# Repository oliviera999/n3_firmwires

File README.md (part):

# Firmwires – Projets ESP32 et Arduino (PlatformIO)

*Contexte : [salle aérée n³](https://n3.olution.info) · Données : [iot.olution.info](https://iot.olution.info). Voir [README racine](../README.md), [RECOMMANDATIONS_IOT](../RECOMMANDATIONS_IOT.md), [inventaire des appareils](../docs/inventaire_appareils.md).*

Dépôt regroupant **plusieurs firmwares** : deux projets principaux ESP32 (serre/aquaponie, station météo), trois projets ESP32-CAM d’envoi de photos vers un serveur web, et le kit **ratata** (ZYC0108-EN) avec exemples Arduino UNO et ESP32-CAM. Chaque projet (ou environnement) est compilable avec **PlatformIO**.

## Projets

| Projet | Dossier | Carte | Description |
|--------|---------|-------|-------------|
| **N3PhasmesProto (n3pp)** | `n3pp/` | ESP32 dev | Contrôle serre / aquaponie : température/humidité air, 4 capteurs humidité sol, pompe, luminosité, mails d’alerte, serveur web, NTP, OLED, deep sleep. |
| **MeteoStationPrototype (msp)** | `msp/` | ESP32 dev | Station météo + tracker solaire : 2× DHT, humidité sol, pluie, DS18B20, 4 LDR, 2 servos, relais, mail, serveur web, NTP, OLED. |
| **Upload Photos (unifié)** | `uploadphotosserver/` | ESP32-CAM | Un seul code, trois envs : **msp1** (msp1gallery, OTA distant HTTP, deep sleep 600 s, version courante `2.39`), **n3pp** (n3ppgallery, deep sleep 600 s, SD), **ffp3** (ffp3gallery, deep sleep 600 s). Upload et contrôle distant au réveil avec `X-Api-Key` (GET état outputs + POST version firmware, aligné serveur ≥ 5.0.306), retries de connexion, vérification du code HTTP retour. Tables `UploadPhoto*Outputs` (boards 5/6/7). Notifications mail SMTP (credentials partagés) : **une fois** au premier démarrage réel (hors réveil deep sleep, flag NVS `upcam/fb_mail`), démarrage/fin OTA, transitions matin/soir du créneau photo. `pio run -e msp1` / `-e n3pp` / `-e ffp3`. |
| **Upload Photos legacy** | `archive/uploadphotosserver_legacy/` | ESP32-CAM | Historique (`uploadphotosserver_*`) conservé en archive ; utiliser uniquement `uploadphotosserver/`. |
| **FFP5CS (aquaponie)** | `ffp5cs/` | ESP32 / ESP32-S3 | Contrôleur aquaponie (WROOM/S3), modulaire, API FFP3, réseau offline-first. Depuis v14.24, la sync distante WROOM utilise un document JSON dédié 2048 o pour absorber le payload `outputs/state` étendu (GPIO 118-123). Build WROOM plus complexe que n3pp/msp (pioarduino 2 passes) — voir [ffp5cs/docs/technical/COMPILATION_WROOM_PIOARDUINO_ET_ENVS.md](ffp5cs/docs/technical/COMPILATION_WROOM_PIOARDUINO_ET_ENVS.md). |
| **Poissonglouton (recyclage)** | `poissonglouton/` | ESP32-S3 | Compteur de bouteilles pour poubelle ludique : détection IR + ultrason (simple ou tandem), feedback audio I2S JC4827W543 (sortie speak), mode écran tactile ou headless, upload batch vers `/pgl/post-data`, heartbeat `/pgl/heartbeat` (flag `PGL_ENABLE_SERVER_HEARTBEAT`), deep sleep solaire. |
| **Banc énergie (INA226)** | `energie/` | ESP32-S3 | Banc d'essai des moniteurs de puissance INA226 du futur module d'aquaponie autonome (carte n3-universal) : panneau solaire / batterie plomb-AGM 12 V / consommation, mesure 1 Hz, POST 10 s vers `/energie-test/post-data` (famille serveur `energie`), SoC + alerte mail batterie basse, console série de calibration. Brique partagée `shared/n3_power`. Voir [energie/README.md](energie/README.md). |
| **LVGL_Widgets** | `à voir/LVGL_Widgets/` | ESP32-S3 | Interface écran tactile ; pas de serveur dédié. Dossier `à voir/` (prototype non maintenu en production). |
| **Ratata (ZYC0108-EN)** | `à voir/ratata/` | 7× UNO, 1× ESP32-CAM | Huit exemples : déplacement, servo, ultrason, évitement, suivi de ligne, voiture caméra WiFi. Dossier `à voir/`. |

## Prérequis

- [PlatformIO](https://platformio.org/) (CLI ou extension VSCode/Cursor) — **Core 6.1.19** (version épinglée en CI) :
  `pip install "platformio==6.1.19"`. PlatformIO **6.2.0** casse les builds ffp5cs WROOM pioarduino
  (`ModuleNotFoundError: SCons.Tool.FortranCommon` : tool-scons 4.8.1 remplacé par 4.11.1 en plein build).
- Selon le projet : carte **ESP32** (esp32dev), **ESP32-CAM** (esp32cam), ou **Arduino UNO** (uno)

## Compilation et upload

Chaque projet se compile et s’upload depuis **son dossier** :

```bash
# N3PhasmesProto (n3pp)
cd n3pp
pio run
pio run -t upload
pio device monitor

# MeteoStation (msp)
cd msp
pio run
pio run -t upload
pio device monitor

# Upload photos (ESP32-CAM unifié) – cible msp1, n3pp ou ffp3
cd uploadphotosserver
pio run -e msp1
pio run -e msp1 -t upload
pio device monitor -e msp1
# Ou : -e n3pp, -e ffp3 selon la galerie cible.

# Poissonglouton (ESP32-S3)
cd poissonglouton
pio run -e pgl-s3-headless
pio run -e pgl-s3-display
pio run -e pgl-s3-jc3248
pio run -e pgl-s3-headless -t upload

# Ratata – compiler un environnement (ex. 1_auto_move ou 6_1_esp32_car)
cd ratata
pio run -e 1_auto_move
pio run -e 1_auto_move -t upload
pio device monitor -e 1_auto_move
```

Adapter `upload_port` et `monitor_port` dans chaque `platformio.ini` (ex. `COM3`, `COM4`, `/dev/ttyUSB0`) selon ta machine.

## Build Windows : chemins courts, redirection et nettoyage

- **Redirection des artefacts** : les projets qui incluent `firmwires/scripts/pio_redirect_build_dir.py` (**ffp5cs**, **n3pp**, **msp**, **uploadphotosserver**, dossiers **test psram s3***) placent les binaires sous `C:\pio-builds\<slug-projet>\<env>\` sur Windows par défaut (évite chemins longs et soucis d’espaces dans le clone). **Linux / CI** : pas de redirection sauf si la variable d’environnement `N3_PIO_BUILD_ROOT` est définie — les artefacts restent alors sous `.pio/build/<env>/` (comportement GitHub Actions inchangé).
- **Désactiver la redirection** : `N3_PIO_BUILD_REDIRECT=0` (PowerShell : `$env:N3_PIO_BUILD_REDIRECT='0'`). **Autre racine** : `N3_PIO_BUILD_ROOT=D:\mes-builds`.
- **Chemins côté scripts** : `firmwires/scripts/Get-PioBuildHelpers.ps1` (fonctions `Get-N3PioFirmwareBin`, etc.) — utilisé par `IOT_n3/scripts/publish_ota.ps1` pour trouver `firmware.bin` / `littlefs.bin` que le build soit sous `C:\pio-builds` ou dans `.pio/build`.
- **Audit build (taille, duree, anomalies)** : `firmwires/scripts/Invoke-PioBuildAudit.ps1` pour mesurer les deltas avant/apres compilation (`BUILD_DIR`, `.pio/libdeps/<env>`, artefacts `firmware.bin`/`firmware.elf`), signaler les anomalies (taille, temps, chemins longs, espace disque) et ecrire un rapport texte.
- **Nettoyage global** : depuis la racine **IOT_n3**, `.\scripts\clean-firmware-builds.ps1` (ajouter `-WhatIf` pour simulation). Options : `-SyncPioBuilds` (purge aussi `C:\pio-builds\<slug>`), `-IncludeLegacyFfp5Mirror` pour `C:\ffp5cs_build`. **Alternance n3pp/ffp5cs** : ne pas nettoyer entre chaque build — utiliser `.\firmwires\scripts\Invoke-PioBuildFast.ps1`.
- **Cache compilation ffp5cs** : `build_cache_dir = C:/pio-builds/.pio-cache/ffp5cs` dans `ffp5cs/platformio.ini`.
- **S3 + espaces dans le chemin** : `ffp5cs/run_s3_build_from_safe_path.bat` (miroir sous `C:\pio-builds\ffp5cs-space-mirror` par défaut) ou `run_s3_fix_via_subst.bat` (lecteur `P:`).
- **Toolchain GCC 14 (Xtensa) + Arduino-ESP32 3.3.x** : erreur de link `undefined reference to __atomic_fetch_add_4` (libstdc++ / `shared_ptr` dans Network, FS, SD) — fichier `src/gcc_atomic_compat.c` dans **n3pp**, **msp** et **uploadphotosserver**. **ESP Mail Client** sur partition SPIFFS uniquement : script `firmwires/scripts/pio_patch_esp_mail_fs_spiffs.py` (référencé par **n3pp**, **msp** et **uploadphotosserver**), qui patche une fois `ESP_Mail_FS.h` dans `.pio/libdeps` (idempotent).

Les projets **legacy** caméra (`uploadphotosserver_*` hors dépôt unifié) ou exemples sans `platformio.ini` à la racine peuvent encore compiler uniquement sous `.pio/build/` : ajouter la même ligne `pre:../scripts/pio_redirect_build_dir.py` si besoin.

Exemple (depuis la racine `firmwires/`, build + audit sur `uploadphotosserver` env `msp1`) :

```powershell
.\scripts\Invoke-PioBuildAudit.ps1 `
  -ProjectRoot .\uploadphotosserver `
  -Environment msp1 `
  -PioArguments run,-e,msp1 `
  -MaxDurationSeconds 900 `
  -MaxBuildGrowthPercent 250
```

## Scripts de monitoring et erase-flash

### Référence FFP5CS (workflow complet)

Le projet **ffp5cs** définit le workflow de validation de référence, aligné sur les règles cœur de projet (offline-first, robustesse, vérification après modification) :

- **Workflow complet** : erase flash → flash firmware (+ LittleFS sauf prod) → monitoring N min → analyse du log. Script principal : `ffp5cs/erase_flash_fs_monitor_5min_analyze.ps1` (options `-Port`, `-Environment`, `-DurationMinutes`, `-SkipBuild`, `-NoPrompt`). Pour **ESP32-S3**, utiliser `-Environment wroom-s3-test` ou `-Environment wroom-s3-prod` ; scripts dédiés : `ffp5cs/run_s3_validation.ps1`, `ffp5cs/run_s3_psram_validation.ps1`, `ffp5cs/run_wroom_s3_prod_workflow.ps1`.
- **Monitoring** : `ffp5cs/monitor_5min.ps1` — capture série N secondes. Les logs et rapports d'analyse sont écrits dans le dossier dédié `ffp5cs/logs/` (plus à la racine du projet).
- **Monitoring crash/reboot** : `ffp5cs/monitor_until_crash.ps1` (wrapper PowerShell) appelle `ffp5cs/tools/monitor/monitor_until_crash.py` pour capturer jusqu'au crash/reboot, puis générer un rapport.
- **Analyse des logs** : `ffp5cs/analyze_log.ps1` (détaillée, spécifique FFP5CS/FFP3) et `ffp5cs/analyze_log_exhaustive.ps1` (crashes, WDT, heap, réseau, reboots). Rapport diagnostic : `ffp5cs/generate_diagnostic_report.ps1`. Toutes les sorties (fichiers .log, _analysis.txt, rapports .md) sont dans `ffp5cs/logs/`.

Pour tout travail sur **ffp5cs**, utiliser ces scripts depuis le dossier `ffp5cs/`. Voir aussi `ffp5cs/.cursor/rules/` et `ffp5cs/docs/INVENTAIRE_SCRIPTS_FFP5CS.md` pour l'inventaire des scripts.

- **Compilation de tous les envs** (évite les builds WROOM pioarduino en parallèle, qui peuvent corrompre le cache) : `ffp5cs/scripts/build_all_envs.ps1`.
- **Guide compilation FFP5CS WROOM** (pioarduino phase 2, secours `wroom-prod-pio6`, flash cohérent, vs n3pp/msp) : [ffp5cs/docs/technical/COMPILATION_WROOM_PIOARDUINO_ET_ENVS.md](ffp5cs/docs/technical/COMPILATION_WROOM_PIOARDUINO_ET_ENVS.md).
- **wroom-beta-local** (build, flash CP210x, tests Docker) : [ffp5cs/docs/technical/WROOM_BETA_LOCAL_BUILD_FLASH_TEST.md](ffp5cs/docs/technical/WROOM_BETA_LOCAL_BUILD_FLASH_TEST.md).
- **Compilation de tous les envs + beta-local** : `ffp5cs/scripts/build_all_envs.ps1 -IncludeBetaLocal`.
- **Build + upload + monitor beta-local** : `ffp5cs/build_upload_monitor_wroom_beta_local.ps1 -Port COM5` (raccourci COM4 : `build_upload_monitor_wroom_beta_local_com4.ps1`). Guide : [WROOM_BETA_LOCAL_BUILD_FLASH_TEST.md](ffp5cs/docs/technical/WROOM_BETA_LOCAL_BUILD_FLASH_TEST.md).
- **Tests unitaires natifs (Unity)** : `pio test -c platformio-native.ini -e native` depuis `ffp5cs/`, ou `ffp5cs/scripts/test_unit_all.ps1` (suites `test_config`, `test_nvs`, `test_server_url`).
- **Tests beta-local sur cible** : `ffp5cs/scripts/test_wroom_beta_local_serial.ps1` (upload + monitor + assertions logs).
- **Tests integration locale Docker + appareil** : `ffp5cs/scripts/test_wroom_beta_local_docker_integration.ps1` (stack docker, override URL LAN local, verification BDD).
- **Batterie de tests beta-local** : `ffp5cs/scripts/run_wroom_beta_local_test_suite.ps1` (secrets optionnels : copier `ffp5cs/scripts/.beta-local-test.env.example` vers `ffp5cs/scripts/.beta-local-test.env`).

### Scripts racine firmwires (multi-projets)

- `firmwires/scripts/analyze_log_generic.ps1` est **versionné** (Phase 5 audit 2026-05) : utilisable pour n3pp, msp, uploadphotosserver. Il prend `-LogFile <chemin>` et produit un rapport texte synthétique (crashes, WDT, heap, réseau).
- Les wrappers `firmwires/monitor_Nmin.ps1` et `firmwires/erase_flash_monitor.ps1` ne sont pas encore présents : utiliser `pio device monitor` / `pio run -t upload` depuis chaque dossier de firmware, ou s'inspirer du workflow ffp5cs.

| Emplacement | Rôle |
|-------------|------|
| `ffp5cs/scripts/Release-ComPort.ps1` | Libération du port COM (processus moniteur). |

**Exemples (référence ffp5cs, depuis `ffp5cs/`) :**

```powershell
# Workflow complet : erase, flash, LittleFS (sauf prod), monitor, analyse
.\erase_flash_fs_monitor_5min_analyze.ps1 -Environment wroom-test -Port COM4

# Monitoring seul
.\monitor_5min.ps1 -Port COM4
```

### Uploadphotosserver — build multi-env

Le firmware caméra unifié dispose d'un script de build multi-env : `uploadphotosserver/scripts/build_all_envs.ps1`.
Commandes directes possibles depuis `uploadphotosserver/` :

- `pio run -e msp1`
- `pio run -e n3pp`
- `pio run -e ffp3`
- **ESP32-CAM (uploadphotosserver)** : `pio run -e msp1` / `-e n3pp` / `-e ffp3` — **platformio/espressif32@6.13.0** + **`board = esp32cam`** (PSRAM + **HTTPS** par défaut depuis v2.54). Broches dans `uploadphotosserver/include/config.h`.
- **Monitoring 1–2 min** (série fiable sous Windows : DTR/RTS désactivés) : depuis `uploadphotosserver/`, `python tools/monitor_serial_cam.py COM5 -s 120` — fermer tout autre moniteur / outil sur le même COM ; dépendance : `pip install pyserial`.
- **Erase + flash + monitor** (camera) : `uploadphotosserver/scripts/erase_flash_monitor.ps1 -Environment msp1 -Port COM5 -DurationSeconds 300`.

## Stack ESP-IDF et plateforme

Tous les firmwares utilisent le **framework Arduino**. La chaîne de build est : plateforme → arduino-esp32 → ESP-IDF (sous-jacent).

**Versions arduino-ESP32 par type d'env :**
- **WROOM** (ffp5cs wroom-prod/test/beta, msp, n3pp) et **poissonglouton** (S3) : **arduino-esp32 3.3.7** (ESP-IDF 5.5.2) via la **plateforme pioarduino** ([pioarduino/platform-espressif32](https://github.com/pioarduino/platform-espressif32) release 55.03.37). Choix : stack IDF 5.x et alignement avec tous les firmwares WROOM du dépôt (uploadphotosserver, ESP32-CAM, reste en 6.13 : ci-dessous).
- **FFP5CS prod secours** : env **`wroom-prod-pio6`** = `espressif32@6.13.0` + Arduino **2.0.17** (build **1 passe**, sans pioarduino) si la phase 2 de `wroom-prod` échoue — détails et tutoriel : [COMPILATION_WROOM_PIOARDUINO_ET_ENVS.md](ffp5cs/docs/technical/COMPILATION_WROOM_PIOARDUINO_ET_ENVS.md).
- **uploadphotosserver** (ESP32-CAM) : envs **`msp1` / `n3pp` / `ffp3`** uniquement — **espressif32@6.13** + **`esp32cam`** + **HTTPS** (`USE_HTTPS_ENDPOINTS`) + diagnostic PSRAM au boot. Anciens envs `*-cam` et `msp1-https` supprimés (v2.54). Voir `uploadphotosserver/README.md` et `docs/HTTPS_MIGRATION.md`.
- **S3** (ffp5cs `wroom-s3-*`, y compris les envs PSRAM `wroom-s3-test-psram*` / `-devkit`, et **energie**) : **plateforme platformio/espressif32@6.13.0**, arduino-esp32 2.0.17 (bundlé, ESP-IDF 4.4.7). Alignement pioarduino possible à terme (erreur linker « gap » à résoudre).

Le **premier build** des projets WROOM télécharge la plateforme pioarduino (~500 Mo) ; en cas d'erreur de verrouillage de fichier (WinError 32/183), fermer les processus PlatformIO/IDE puis relancer.

### Recovery PlatformIO Windows (WROOM / esp32cam)

En cas d'erreur intermittente du type `TypeError: _path_exists ... NoneType` ou `FRAMEWORK_DIR None` :

1. Fermer Cursor/VSCode, tout moniteur série et tous les terminaux qui compilent/flashing.
2. Depuis `firmwires/`, lancer un build de warmup sur un firmware WROOM stable :
   - `cd n3pp`
   - `pio run -e esp32dev`
3. Revenir au firmware cible et relancer le build :
   - `cd ../uploadphotosserver`
   - `pio run -e msp1` (ou `-e n3pp`, `-e ffp3`)
4. Si l'erreur persiste : nettoyer le cache/framework PlatformIO local puis relancer la séquence warmup + build cible.
5. Sous Windows, éviter les builds parallèles pioarduino sur plusieurs projets en même temps.

Détails et APIs ESP-IDF utilisées en direct (ffp5cs) : [RECOMMANDATIONS_IOT.md § 2.9](../RECOMMANDATIONS_IOT.md#29-stack-esp-idf-et-conventions).

## Configuration des ports série

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
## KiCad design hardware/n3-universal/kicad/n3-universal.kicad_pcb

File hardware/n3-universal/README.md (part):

# n3-universal — étude de faisabilité (étape 0)

Projet : **une carte porteuse commune** aux trois systèmes (msp station météo,
n3pp serre/élevage, ffp5cs aquaponie), bi-module (site A1 WROOM DevKitC 38 broches /
site A2 ESP32-S3-DevKitC-1 — rev 0.2.3), 12/24 V, avec :
- rail capteurs commuté `+3V3_SW` (rev 0.2 : **LDO dédié U1 LD1117V33** derrière le
  P-FET Q7 IRF4905, **jumper bypass JP1 fermé par défaut** — ffp5cs, toujours alimenté,
  ne pilote pas le gate) et pont diviseur VBAT **permanent** (R38 + JP12 18k/100k — 22k jusqu'à la 0.2.1) ;
- bloc solaire TP4056 + 18650 en option de peuplement (msp/n3pp) ;
- RTC **DS3231** : VCC du module sur **`+3V3_SW`** (coupé en veille — PAS de rail
  permanent nécessaire) : le chip bascule nativement sur sa **pile bouton** et
  continue de compter (~3 µA, compensation température maintenue, CR2032 ≈ 8 ans) ;
  l'I2C est inaccessible sous VPF par conception (pas de fuite vers le rail éteint,
  pull-ups déjà sur `+3V3_SW`). Au réveil le firmware relit l'heure et resynchronise
  l'horloge interne (dérive deep sleep de l'ESP32 : minutes/jour → DS3231 ±2 ppm).
  Peuplement modules ZS-042 : **neutraliser le circuit de charge** (diode+200 Ω prévus
  LIR2032 — dessouder, monter une CR2032) et retirer la LED d'alim du module.
- slot **microSD unique** câblé aux deux sites : natif côté S3, et côté WROOM sur des
  nets inutilisés par msp/n3pp (CS=14/US3, CLK=23/AUX1, MOSI=25/AUX2, MISO=12 sans
  pull-up) — **msp et n3pp ont la SD sans rien sacrifier** ; seul ffp5cs-sur-WROOM
  arbitre par env de build (futur env `wroom-sd`, à créer au besoin : SD contre US_POTA+AUX), RTC **DS3231** et **3 INA226**
  sur I2C (INA alimentés par `+3V3_SW`) ;
- le **230 V reste hors périmètre** : la carte `ffp5cs-wroom-prod-230v` existante
  demeure la variante secteur (sécurité, 2 oz, distances de fuite).

> 🟢 **Rev 0.2 (2026-10-07)** (→ remplacée par la 0.2.2 puis la 0.2.3) — régénérée de bout en bout (schéma,
> placement, routage, gerbers 2 oz) après la contre-vérification de la 0.1.2 (audit §13 :
> repères de sérigraphie décalés, J29/J30 sous le DevKit, Q7 NDP6020P introuvable). Ce qui
> change et pourquoi : tableau « 0.1.2 → 0.2 » ci-dessous ; contrôles : audit §14 ;
> dossier de fabrication : `exports/gerbers-n3-universal-v0.2.zip`.
>
> 📋 **Avant de commander** : lire **[`COMMANDE.md`](COMMANDE.md)** (options exactes du
> formulaire JLCPCB, devis du 2026-10-30, pourquoi pas de colis LCSC vers le Maroc, et procédure
> de devis PCB Maroc) et **[`AUDIT-2026-08-28.md`](AUDIT-2026-08-28.md)** (contre-vérification
> pré-commande : verdict, constats retenus, check-list rev 0.2). Fichiers d'assemblage
> éventuel : [`exports/pcba/`](exports/pcba/).
>
> 🟢 **Rev 0.2.3 (2026-10-31) = version à commander** : site A1 en **ESP32 DevKitC 38 broches**,
> rangées droites d'A1 et A2 doublées 25,4 / 22,86 mm, carte reroutée (section « Rev 0.2.3 »
> ci-dessous). Fichier : `exports/gerbers-n3-universal-v0.2.3.zip` ; le zip 0.2.2 est périmé.
>
> 🔶 **Cuivre 1 oz depuis le 2026-10-30** (ex-2 oz, −58 $ sur 10 cartes) : les charges réelles
> (pompes, chauffage d'aquarium ≤ 300 W) sont loin de la limite des pistes contacts 2,5 mm en
> 1 oz (≈ 4,5 A à +10 °C). Règle d'usage : **≤ 1 kW résistif / 3 A moteur par canal**
> (`COMMANDE.md` §1 et §5). Empilage 1 oz porté par le `gbrjob` du zip. Résultats JLCDFM
> (v0.2.3) et lignes attendues dans `COMMANDE.md` §0.
>
> 🧭 [`EVOLUTIONS_PROPOSEES.md`](EVOLUTIONS_PROPOSEES.md) : l'étude du sélecteur AUTO / ON,
> du retour d'état et de la connectique — **décisions actées le 2026-10-06 et appliquées
> en 0.2** (encadré en tête du document).
>
> ⛔ **Rev 0.2.2 (2026-10-17) — NE PAS COMMANDER la 0.2** : la simulation SPICE
> ([`simulation/SIMULATION.md`](simulation/SIMULATION.md)) a montré que **Q7 (IRF4905, rail
> capteurs) était câblé à l'envers** (drain sur +5V, source sur LDO_IN : la diode interne
> alimente le LDO en permanence, le rail ne se coupe jamais sur les profils msp/n3pp).
> Corrigé dans `generate.py` (source = +5V, drain = LDO_IN), schéma + BOM régénérés, garde
> `tools/check_fet_orientation.py`, champs `Sim.*` (schéma simulable dans KiCad). **Le PCB
> routé n'est pas encore à jour** : voir « Rev 0.2.1 » ci-dessous.

## Rev 0.2.3 — site A1 en DevKitC 38 broches (2026-10-31) : carte reroutée

Les modules WROOM disponibles sont des **ESP32 DevKitC 38 broches** (rangées mesurées à **25,4 mm**
d'axe en axe), plus un clone S3 DevKitC-1 double USB-C. Le site A1 de la 0.2.2 (DevKit V1
30 broches) ne les acceptait pas. Firmwares inchangés : chaque fonction garde son GPIO, seules les
positions physiques des pastilles changent (garde `check_pinmap_vs_firmware` étendue).

| Changement | Pourquoi | Conséquence d'usage |
|---|---|---|
| **A1 = empreinte `ESP32_DevKitC_38pin`** (2 × 19, pas 2,54) : rangée gauche x 100, **rangée droite doublée** à 25,4 mm (principale) **et** 22,86 mm (secours), pontées pastille à pastille | 25,4 mm mesuré sur les modules ; 22,86 mm = autre largeur courante des clones 38 broches | barrettes femelles 1×19 : la gauche, et la droite dans la rangée qui correspond au module (25,4 par défaut) ; **ne jamais garnir les deux rangées droites** |
| **A2 (S3 DevKitC-1, 2 × 22)** : rangée droite aussi doublée 25,4 / 22,86 | les clones S3 existent dans les deux largeurs | idem : une seule rangée droite garnie |
| Brochage A1 (DevKitC) : GPIO 6-11 (flash) et GPIO0 **non câblés** ; EN, 3V3, 5V, GND aux positions DevKitC | broches flash interdites ; GPIO0 = boot | garde : `WROOM_FORBIDDEN`, `WROOM_POWER`, rangées doublées sur le même net (`DUP_MISMATCH`) |
| A1 replacé (100 ; 108,46), A2 (257 ; 129,2), zone interdite d'antenne A1 recalculée | dégagement d'enfichage et d'antenne | `check_pcb_clearance` (couloirs d'enfichage) ✅ |
| Notes de profil au dos raccourcies (≤ 21 caractères) et recentrées entre les rangées d'A1 | la rangée de secours à 22,86 mm passe sous les anciennes notes | lecture inchangée (« JP1 + JP13-15 fermes »…) |

**Routage 0.2.3** : reroutage complet à blanc (freerouting 2.5.0, ponts des rangées doublées posés
avant routage) : **0 net non routé** dès la passe 11 ; secteur, vias de couture et thermals régénérés
par `route_universal.py`. 7 étranglements de freerouting (0,20-0,24 mm) relevés à 0,25 mm et un
tronçon VBAT_DIV rerouté sous JP12 (écart au pad 3). Bilan : 2 603 segments, 146 vias, 14,1 m de
piste (0.2.2 : 121 vias, 14,2 m). `tidy_silkscreen` : exception explicite `KEEP_ON_VIAS` (l'étiquette
« 3V3 » de TP4 reste sur deux vias EN tentés, sinon elle prenait la place du repère TP4).

| Contrôle (KiCad 10.0.8 Linux, 2026-10-31) | Rev 0.2.3 |
|---|---|
| ERC | 0 erreur |
| DRC + parité schéma | **0 erreur, 0 non connecté, 0 écart de parité**, 64 avertissements de sérigraphie (62 en 0.2.2 : textes contre des vias tentés) |
| `check_mains_gap` / plan GND ↔ secteur | 0 écart < 3 mm ; plans à 6,50 mm |
| Gardes | `check_fet_orientation` ✅ ; `check_pinmap_vs_firmware` ✅ (tables DevKitC 38, GPIO flash, rangées doublées) ; `check_silk_refs` ✅ ; `check_pcb_clearance` ✅ ; `annotate_pcb_roles --check` ✅ ; `sync_pcb_sim_fields --check` ✅ ; `check_jlcpcb_caps` ✅ ; `tidy_silkscreen` : 0 déplacement ; générateur idempotent ✅ ; `achats --check` ✅ ; `fritzing --check` ✅ |
| Banc SPICE sur la netlist KiCad | rail capteurs 0 V / 3,30 V ✅ |
| `exports/` | **gerbers v0.2.3** (`export_fab.py --rev 0.2.3`, DRC bloquant passé), PDF/SVG, BOM/CPL ; zip 0.2.2 retiré |

## Rev 0.2.2 — décisions d'alimentation (2026-10-17) : carte reroutée

Après [`ALIMENTATION.md`](ALIMENTATION.md) (sobriété et robustesse des quatre profils, une seule
commande JLCPCB), quatre changements sur la 0.2.1, carte **régénérée et reroutée** par la chaîne
habituelle (`generate.py --regen-pcb` → `route_universal.py` / freerouting 2.1 → tidy →
contrôles → `export_fab.py`) puis revalidée (tableau de contrôles ci-dessous) :

| Changement | Pourquoi | Conséquence d'usage |
|---|---|---|
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
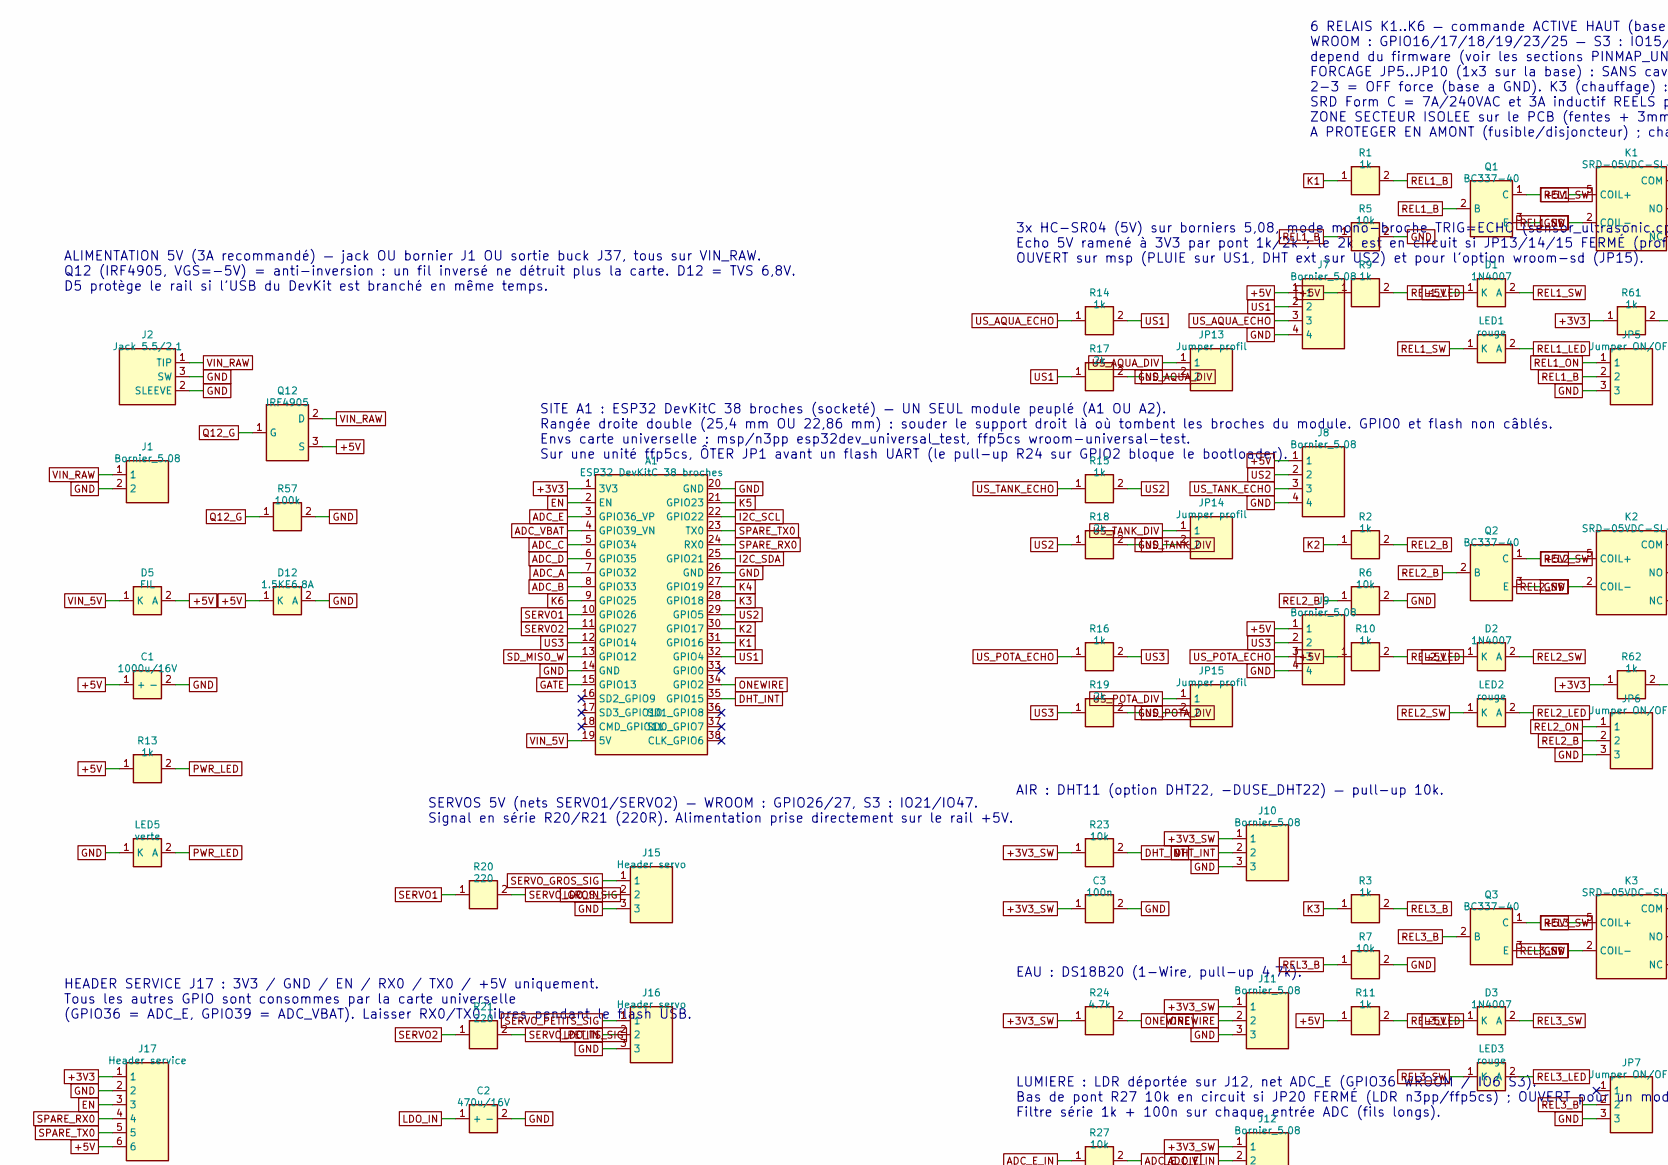
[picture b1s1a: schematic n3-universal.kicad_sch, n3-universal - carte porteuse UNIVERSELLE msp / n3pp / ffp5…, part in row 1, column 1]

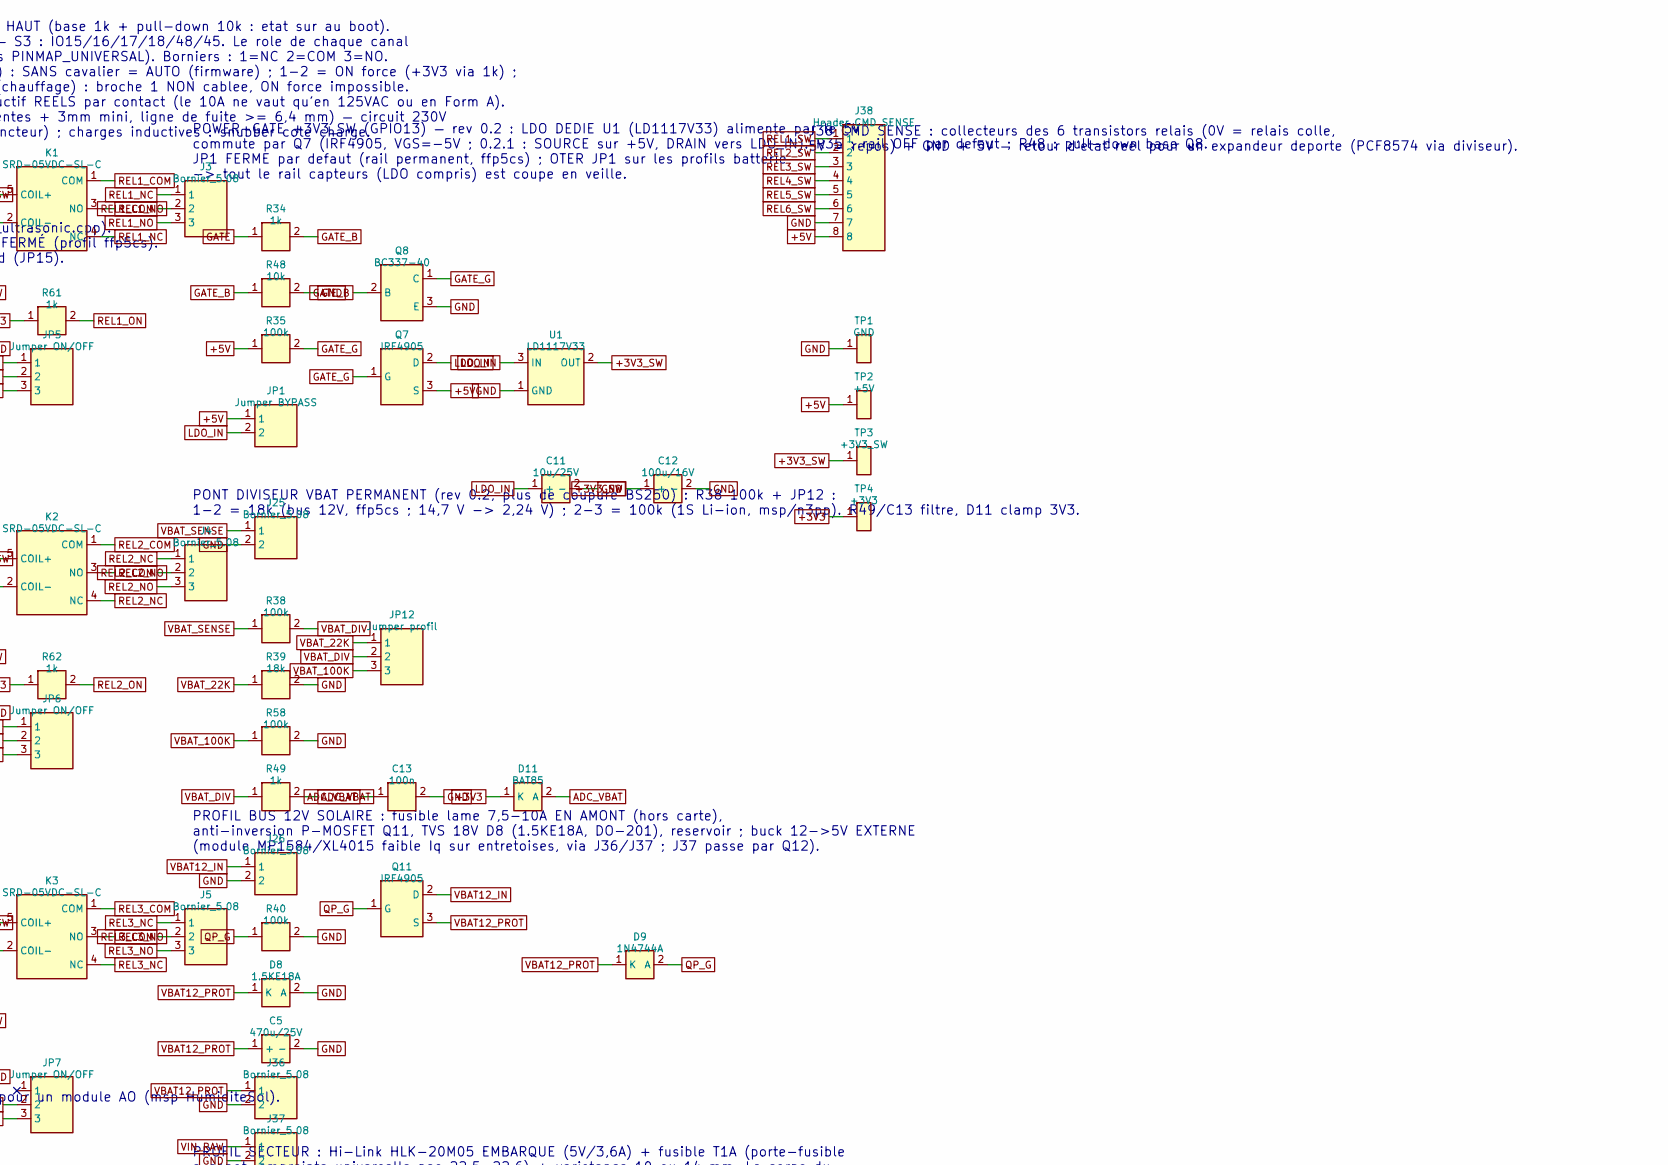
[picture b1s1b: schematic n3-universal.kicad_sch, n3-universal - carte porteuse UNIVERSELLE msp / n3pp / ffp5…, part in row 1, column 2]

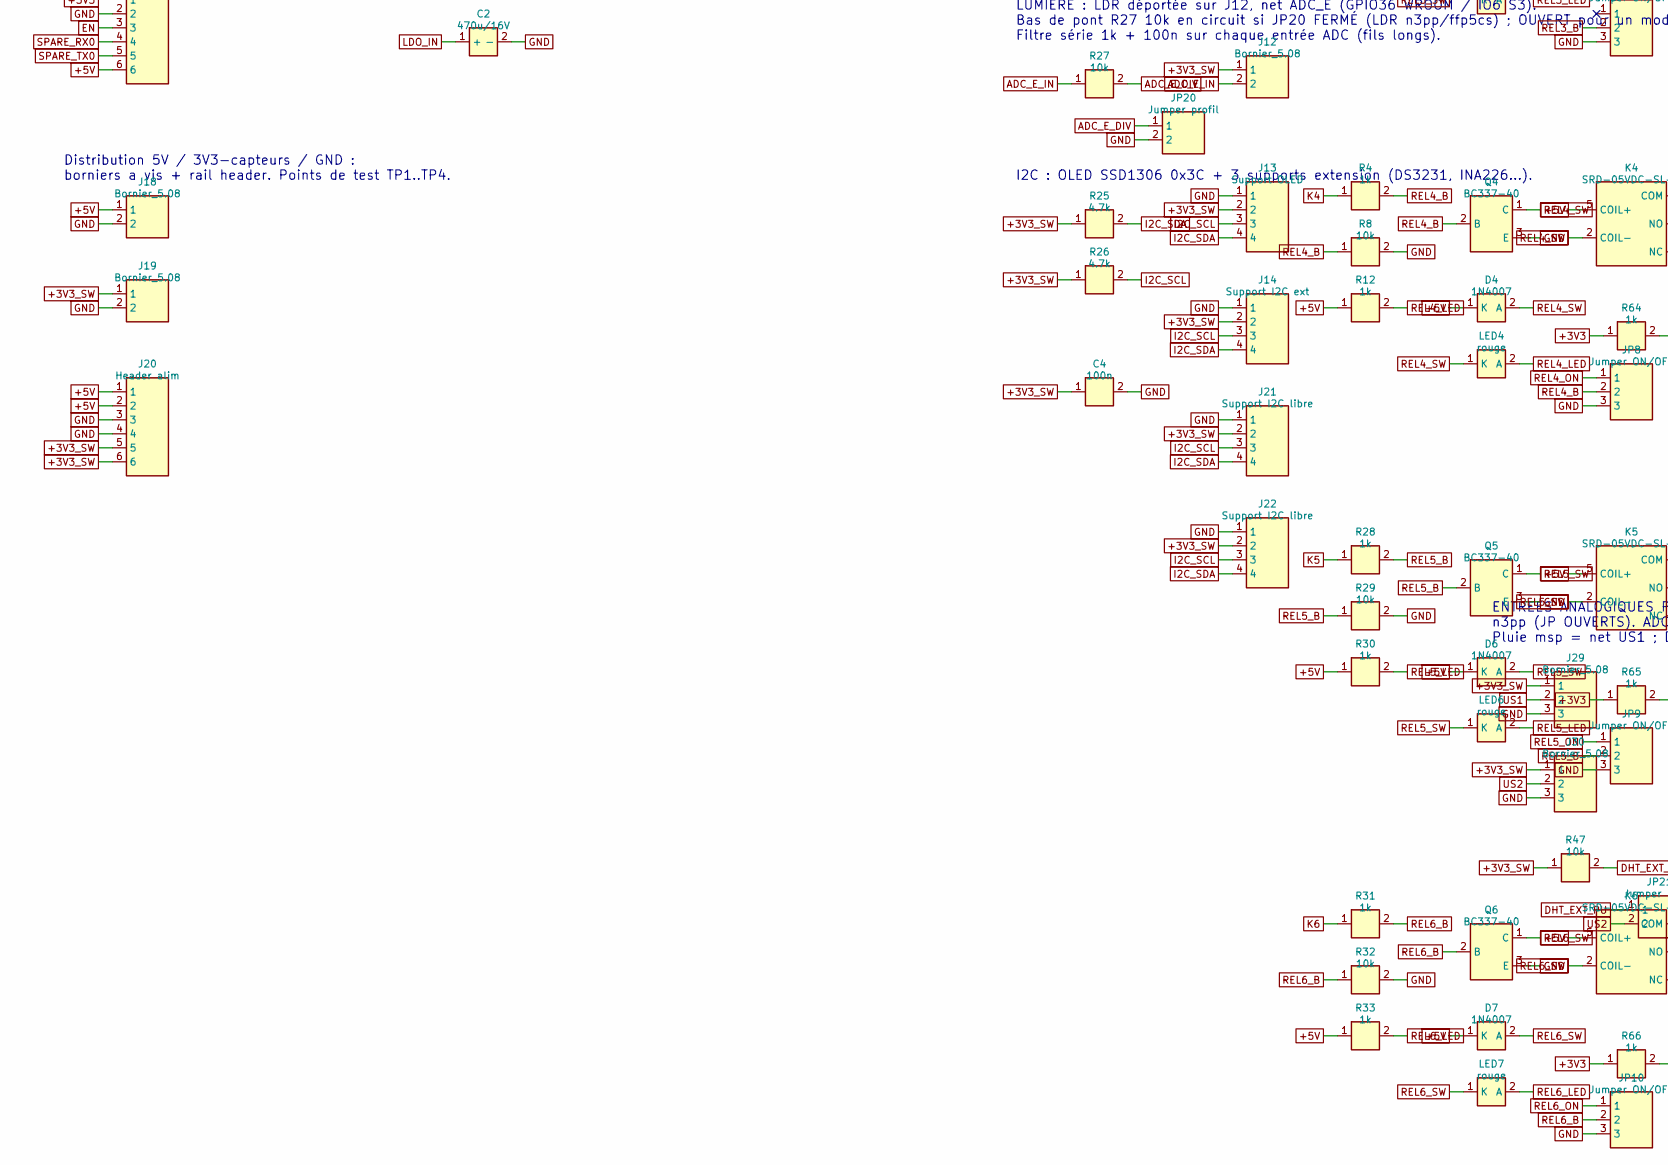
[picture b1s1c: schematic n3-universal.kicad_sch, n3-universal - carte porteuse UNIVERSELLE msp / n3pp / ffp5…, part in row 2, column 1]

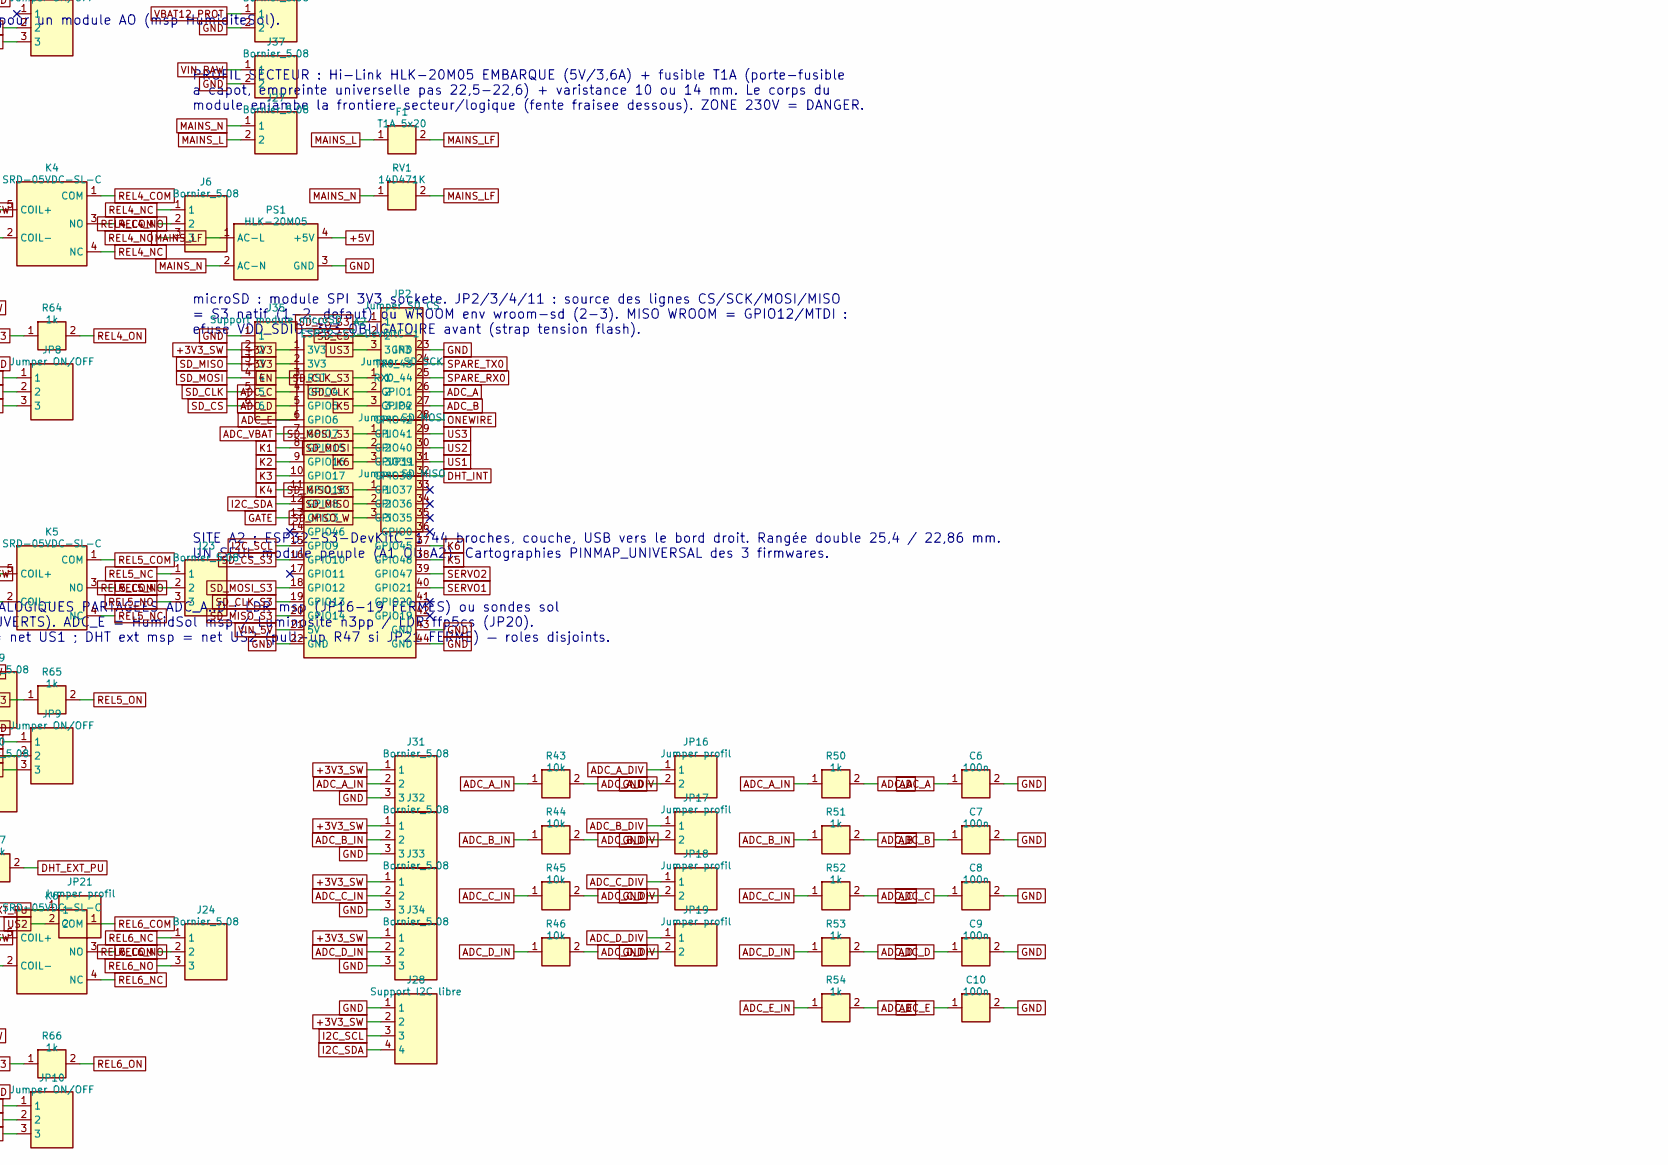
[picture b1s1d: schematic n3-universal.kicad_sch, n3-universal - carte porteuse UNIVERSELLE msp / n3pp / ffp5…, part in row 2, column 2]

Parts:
A1: ESP32 DevKitC 38 broches; ESP32_DevKitC_38pin
A2: ESP32-S3-DevKitC-1; ESP32_S3_DevKitC_1_44pin
C1: 1000u/16V; CP_Radial_D10.0mm_P5.00mm
C2: 470u/16V; CP_Radial_D8.0mm_P3.50mm
C3, C4, C6, C7, C8, C9, C10, C13: 100n; C_Disc_D5.0mm_W2.5mm_P5.00mm
C5: 470u/25V; CP_Radial_D10.0mm_P5.00mm
C11: 10u/25V; CP_Radial_D5.0mm_P2.50mm
C12: 100u/16V; CP_Radial_D6.3mm_P2.50mm
D1, D2, D3, D4, D6, D7: 1N4007; D_DO-41_SOD81_P10.16mm_Horizontal
D5: FIL; D_DO-201AD_P15.24mm_Horizontal
D8: 1.5KE18A; D_DO-201AD_P15.24mm_Horizontal
D9: 1N4744A; D_DO-41_SOD81_P5.08mm_Vertical_AnodeUp
D11: BAT85; D_DO-35_SOD-123_Dual_P7.62mm
D12: 1.5KE6.8A; D_DO-201AD_P15.24mm_Horizontal
F1: T1A 5x20; Fuse_5x20_Universal
J1, J12, J18, J19, J25, J26, J27, J36, J37: Bornier_5.08; TerminalBlock_bornier-2_P5.08mm
J2: Jack 5.5/2.1; BarrelJack_Horizontal
J3, J4, J5, J6, J10, J11, J23, J24, J29, J30, J31, J32, J33, J34: Bornier_5.08; TerminalBlock_bornier-3_P5.08mm
J7, J8, J9: Bornier_5.08; TerminalBlock_bornier-4_P5.08mm
J13: Support OLED; PinSocket_1x04_P2.54mm_Vertical
J14: Support I2C ext; PinSocket_1x04_P2.54mm_Vertical
J15, J16: Header servo; PinHeader_1x03_P2.54mm_Vertical
J17: Header service; PinHeader_1x06_P2.54mm_Vertical
J20: Header alim; PinHeader_1x06_P2.54mm_Vertical
J21, J22, J28: Support I2C libre; PinSocket_1x04_P2.54mm_Vertical
J35: Support module microSD; PinSocket_1x06_P2.54mm_Vertical
J38: Header CMD SENSE; PinHeader_1x08_P2.54mm_Vertical
JP1: Jumper BYPASS; PinHeader_1x03_P2.54mm_Vertical
JP2: Jumper SD CS; PinHeader_1x03_P2.54mm_Vertical
JP3: Jumper SD SCK; PinHeader_1x03_P2.54mm_Vertical
JP4: Jumper SD MOSI; PinHeader_1x03_P2.54mm_Vertical
JP5, JP6, JP7, JP8, JP9, JP10: Jumper ON/OFF; PinHeader_1x03_P2.54mm_Vertical
JP11: Jumper SD MISO; PinHeader_1x03_P2.54mm_Vertical
JP12: Jumper profil; PinHeader_1x03_P2.54mm_Vertical
JP13, JP14, JP15, JP16, JP17, JP18, JP19, JP20, JP21: Jumper profil; PinHeader_1x02_P2.54mm_Vertical
K1, K2, K3, K4, K5, K6: SRD-05VDC-SL-C; Relay_SPDT_SANYOU_SRD_Series_Form_C
LED1, LED2, LED3, LED4, LED6, LED7: rouge; LED_D5.0mm
LED5: verte; LED_D5.0mm
PS1: HLK-20M05; Converter_ACDC_Hi-Link_HLK-20Mxx
Q1, Q2, Q3, Q4, Q5, Q6, Q8: BC337-40; TO-92_Inline_Wide_CBE
Q7, Q11, Q12: IRF4905; TO-220-3_Vertical_GDS
R1, R2, R3, R4, R9, R10, R11, R12, R13, R14, R15, R16, R28, R30, R31, R33, R34, R49, R50, R51, R52, R53, R54, R61, R62, R64, R65, R66: 1k; R_Axial_DIN0207_L6.3mm_D2.5mm_P10.16mm_Horizontal
R5, R6, R7, R8, R23, R27, R29, R32, R43, R44, R45, R46, R47, R48: 10k; R_Axial_DIN0207_L6.3mm_D2.5mm_P10.16mm_Horizontal
R17, R18, R19: 2k; R_Axial_DIN0207_L6.3mm_D2.5mm_P10.16mm_Horizontal
R20, R21: 220; R_Axial_DIN0207_L6.3mm_D2.5mm_P10.16mm_Horizontal
R24, R25, R26: 4.7k; R_Axial_DIN0207_L6.3mm_D2.5mm_P10.16mm_Horizontal
R35, R38, R40, R57, R58: 100k; R_Axial_DIN0207_L6.3mm_D2.5mm_P10.16mm_Horizontal
R39: 18k; R_Axial_DIN0207_L6.3mm_D2.5mm_P10.16mm_Horizontal
RV1: 14D471K; RV_Disc_D15.5mm_W8mm_P7.5mm
TP1: GND; TestPoint_THTPad_D2.0mm_Drill1.0mm
TP2: +5V; TestPoint_THTPad_D2.0mm_Drill1.0mm
TP3: +3V3_SW; TestPoint_THTPad_D2.0mm_Drill1.0mm
TP4: +3V3; TestPoint_THTPad_D2.0mm_Drill1.0mm
U1: LD1117V33; TO-220-3_Vertical_LDO

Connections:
+3V3: A1.1 (3V3), A2.1 (3V3), A2.2 (3V3), D11.1 (K), J17.1, R61.1, R62.1, R64.1, R65.1, R66.1, TP4.1
+3V3_SW: C3.1, C4.1, C12.1 (+), J10.1, J11.1, J12.1, J13.2, J14.2, J19.1, J20.5, J20.6, J21.2, J22.2, J28.2, J29.1, J30.1, J31.1, J32.1, J33.1, J34.1, J35.2, R23.1, R24.1, R25.1, R26.1, R47.1, TP3.1, U1.2 (OUT)
+5V: C1.1 (+), D1.1 (K), D2.1 (K), D3.1 (K), D4.1 (K), D5.2 (A), D6.1 (K), D7.1 (K), D12.1 (K), J7.1, J8.1, J9.1, J17.6, J18.1, J20.1, J20.2, J38.8, JP1.1, K1.5 (COIL+), K2.5 (COIL+), K3.5 (COIL+), K4.5 (COIL+), K5.5 (COIL+), K6.5 (COIL+), PS1.4 (+5V), Q7.3 (S), Q12.3 (S), R9.1, R10.1, R11.1, R12.1, R13.1, R30.1, R33.1, R35.1, TP2.1
ADC_A: A1.7 (GPIO32), A2.26 (GPIO1), C6.1, R50.2
ADC_A_DIV: JP16.1, R43.2
ADC_A_IN: J31.2, R43.1, R50.1
ADC_B: A1.8 (GPIO33), A2.27 (GPIO2), C7.1, R51.2
ADC_B_DIV: JP17.1, R44.2
ADC_B_IN: J32.2, R44.1, R51.1
ADC_C: A1.5 (GPIO34), A2.4 (GPIO4), C8.1, R52.2
ADC_C_DIV: JP18.1, R45.2
ADC_C_IN: J33.2, R45.1, R52.1
ADC_D: A1.6 (GPIO35), A2.5 (GPIO5), C9.1, R53.2
ADC_D_DIV: JP19.1, R46.2
ADC_D_IN: J34.2, R46.1, R53.1
ADC_E: A1.3 (GPIO36_VP), A2.6 (GPIO6), C10.1, R54.2
ADC_E_DIV: JP20.1, R27.2
ADC_E_IN: J12.2, R27.1, R54.1
ADC_VBAT: A1.4 (GPIO39_VN), A2.7 (GPIO7), C13.1, D11.2 (A), R49.2
DHT_EXT_PU: JP21.1, R47.2
DHT_INT: A1.35 (GPIO15), A2.32 (GPIO38), J10.2, R23.2
EN: A1.2 (EN), A2.3 (RST), J17.3
GATE: A1.15 (GPIO13), A2.13 (GPIO3), R34.1
GATE_B: Q8.2 (B), R34.2, R48.1
GATE_G: Q7.1 (G), Q8.1 (C), R35.2
GND: A1.14 (GND), A1.20 (GND), A1.26 (GND), A2.22 (GND), A2.23 (GND), A2.43 (GND), A2.44 (GND), C1.2 (-), C2.2 (-), C3.2, C4.2, C5.2 (-), C6.2, C7.2, C8.2, C9.2, C10.2, C11.2 (-), C12.2 (-), C13.2, D8.2 (A), D12.2 (A), J1.2, J2.2 (SLEEVE), J2.3 (SW), J7.4, J8.4, J9.4, J10.3, J11.3, J13.1, J14.1, J15.3, J16.3, J17.2, J18.2, J19.2, J20.3, J20.4, J21.1, J22.1, J25.2, J26.2, J28.1, J29.3, J30.3, J31.3, J32.3, J33.3, J34.3, J35.1, J36.2, J37.2, J38.7, JP5.3, JP6.3, JP7.3, JP8.3, JP9.3, JP10.3, JP13.2, JP14.2, JP15.2, JP16.2, JP17.2, JP18.2, JP19.2, JP20.2, LED5.1 (K), PS1.3 (GND), Q1.3 (E), Q2.3 (E), Q3.3 (E), Q4.3 (E), Q5.3 (E), Q6.3 (E), Q8.3 (E), R5.2, R6.2, R7.2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
I2C_SCL: A1.22 (GPIO22), A2.15 (GPIO9), J13.3, J14.3, J21.3, J22.3, J28.3, R26.2
I2C_SDA: A1.25 (GPIO21), A2.12 (GPIO8), J13.4, J14.4, J21.4, J22.4, J28.4, R25.2
K1: A1.31 (GPIO16), A2.8 (GPIO15), R1.1
K2: A1.30 (GPIO17), A2.9 (GPIO16), R2.1
K3: A1.28 (GPIO18), A2.10 (GPIO17), R3.1
K4: A1.27 (GPIO19), A2.11 (GPIO18), R4.1
K5: A1.21 (GPIO23), A2.38 (GPIO48), JP3.3, R28.1
K6: A1.9 (GPIO25), A2.37 (GPIO45), JP4.3, R31.1
LDO_IN: C2.1 (+), C11.1 (+), J15.2, J16.2, JP1.2, Q7.2 (D), U1.3 (IN)
MAINS_L: F1.1, J27.2
MAINS_LF: F1.2, PS1.1 (AC-L), RV1.2
MAINS_N: J27.1, PS1.2 (AC-N), RV1.1
ONEWIRE: A1.34 (GPIO2), A2.28 (GPIO42), J11.2, R24.2
PWR_LED: LED5.2 (A), R13.2
Q12_G: Q12.1 (G), R57.1
QP_G: D9.2 (A), Q11.1 (G), R40.1
REL1_B: JP5.2, Q1.2 (B), R1.2, R5.1
REL1_COM: J3.2, K1.1 (COM)
REL1_LED: LED1.2 (A), R9.2
REL1_NC: J3.1, K1.4 (NC)
REL1_NO: J3.3, K1.3 (NO)
REL1_ON: JP5.1, R61.2
REL1_SW: D1.2 (A), J38.1, K1.2 (COIL-), LED1.1 (K), Q1.1 (C)
REL2_B: JP6.2, Q2.2 (B), R2.2, R6.1
REL2_COM: J4.2, K2.1 (COM)
REL2_LED: LED2.2 (A), R10.2
REL2_NC: J4.1, K2.4 (NC)
REL2_NO: J4.3, K2.3 (NO)
REL2_ON: JP6.1, R62.2
REL2_SW: D2.2 (A), J38.2, K2.2 (COIL-), LED2.1 (K), Q2.1 (C)
REL3_B: JP7.2, Q3.2 (B), R3.2, R7.1
REL3_COM: J5.2, K3.1 (COM)
REL3_LED: LED3.2 (A), R11.2
REL3_NC: J5.1, K3.4 (NC)
REL3_NO: J5.3, K3.3 (NO)
REL3_SW: D3.2 (A), J38.3, K3.2 (COIL-), LED3.1 (K), Q3.1 (C)
REL4_B: JP8.2, Q4.2 (B), R4.2, R8.1
REL4_COM: J6.2, K4.1 (COM)
REL4_LED: LED4.2 (A), R12.2
REL4_NC: J6.1, K4.4 (NC)
REL4_NO: J6.3, K4.3 (NO)
REL4_ON: JP8.1, R64.2
REL4_SW: D4.2 (A), J38.4, K4.2 (COIL-), LED4.1 (K), Q4.1 (C)
REL5_B: JP9.2, Q5.2 (B), R28.2, R29.1
REL5_COM: J23.2, K5.1 (COM)
REL5_LED: LED6.2 (A), R30.2
REL5_NC: J23.1, K5.4 (NC)
REL5_NO: J23.3, K5.3 (NO)
REL5_ON: JP9.1, R65.2
REL5_SW: D6.2 (A), J38.5, K5.2 (COIL-), LED6.1 (K), Q5.1 (C)
REL6_B: JP10.2, Q6.2 (B), R31.2, R32.1
REL6_COM: J24.2, K6.1 (COM)
REL6_LED: LED7.2 (A), R33.2
REL6_NC: J24.1, K6.4 (NC)
REL6_NO: J24.3, K6.3 (NO)
REL6_ON: JP10.1, R66.2
REL6_SW: D7.2 (A), J38.6, K6.2 (COIL-), LED7.1 (K), Q6.1 (C)
SD_CLK: J35.5, JP3.2
SD_CLK_S3: A2.19 (GPIO13), JP3.1
SD_CS: J35.6, JP2.2
SD_CS_S3: A2.16 (GPIO10), JP2.1
SD_MISO: J35.3, JP11.2
SD_MISO_S3: A2.20 (GPIO14), JP11.1
SD_MISO_W: A1.13 (GPIO12), JP11.3
SD_MOSI: J35.4, JP4.2
SD_MOSI_S3: A2.18 (GPIO12), JP4.1
SERVO1: A1.10 (GPIO26), A2.40 (GPIO21), R20.1
SERVO2: A1.11 (GPIO27), A2.39 (GPIO47), R21.1
SERVO_GROS_SIG: J15.1, R20.2
SERVO_PETITS_SIG: J16.1, R21.2
SPARE_RX0: A1.24 (RX0), A2.25 (RX0_44), J17.4
SPARE_TX0: A1.23 (TX0), A2.24 (TX0_43), J17.5
US1: A1.32 (GPIO4), A2.31 (GPIO39), J7.2, J29.2, R14.2, R17.1
US2: A1.29 (GPIO5), A2.30 (GPIO40), J8.2, J30.2, JP21.2, R15.2, R18.1
US3: A1.12 (GPIO14), A2.29 (GPIO41), J9.2, JP2.3, R16.2, R19.1
US_AQUA_DIV: JP13.1, R17.2
US_AQUA_ECHO: J7.3, R14.1
US_POTA_DIV: JP15.1, R19.2
US_POTA_ECHO: J9.3, R16.1
US_TANK_DIV: JP14.1, R18.2
US_TANK_ECHO: J8.3, R15.1
VBAT12_IN: J26.1, Q11.2 (D)
VBAT12_PROT: C5.1 (+), D8.1 (K), D9.1 (K), J36.1, Q11.3 (S)
VBAT_22K: JP12.1, R39.1
VBAT_100K: JP12.3, R58.1
VBAT_DIV: JP12.2, R38.2, R49.1
VBAT_SENSE: J25.1, R38.1
VIN_5V: A1.19 (5V), A2.21 (5V), D5.1 (K)
VIN_RAW: J1.1, J2.1 (TIP), J37.1, Q12.2 (D)

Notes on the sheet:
ALIMENTATION 5V (3A recommandé) — jack OU bornier J1 OU sortie buck J37, tous sur VIN_RAW. Q12 (IRF4905, VGS=-5V) = anti-inversion : un fil inversé ne détruit plus la carte. D12 = TVS 6,8V. D5 protège le rail si l'USB du DevKit est branché en même temps.
SITE A1 : ESP32 DevKitC 38 broches (socketé) — UN SEUL module peuplé (A1 OU A2). Rangée droite double (25,4 mm OU 22,86 mm) : souder le support droit là où tombent les broches du module. GPIO0 et flash non câblés. Envs carte universelle : msp/n3pp esp32dev_universal_test, ffp5cs wroom-universal-tes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
SERVOS 5V (nets SERVO1/SERVO2) — WROOM : GPIO26/27, S3 : IO21/IO47. Signal en série R20/R21 (220R). Alimentation prise directement sur le rail +5V.
3x HC-SR04 (5V) sur borniers 5,08, mode mono-broche TRIG=ECHO (sensor_ultrasonic.cpp). Echo 5V ramené à 3V3 par pont 1k/2k ; le 2k est en circuit si JP13/14/15 FERMÉ (profil ffp5cs). OUVERT sur msp (PLUIE sur US1, DHT ext sur US2) et pour l'option wroom-sd (JP15).
AIR : DHT11 (option DHT22, -DUSE_DHT22) — pull-up 10k.
EAU : DS18B20 (1-Wire, pull-up 4.7k).
LUMIERE : LDR déportée sur J12, net ADC_E (GPIO36 WROOM / IO6 S3). Bas de pont R27 10k en circuit si JP20 FERMÉ (LDR n3pp/ffp5cs) ; OUVERT pour un module AO (msp HumiditeSol). Filtre série 1k + 100n sur chaque entrée ADC (fils longs).
I2C : OLED SSD1306 0x3C + 3 supports extension (DS3231, INA226...).
6 RELAIS K1..K6 — commande ACTIVE HAUT (base 1k + pull-down 10k : etat sur au boot). WROOM : GPIO16/17/18/19/23/25 — S3 : IO15/16/17/18/48/45. Le role de chaque canal depend du firmware (voir les sections PINMAP_UNIVERSAL). Borniers : 1=NC 2=COM 3=NO. FORCAGE JP5..JP10 (1x3 sur la base) : SANS cava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
HEADER SERVICE J17 : 3V3 / GND / EN / RX0 / TX0 / +5V uniquement. Tous les autres GPIO sont consommes par la carte universelle (GPIO36 = ADC_E, GPIO39 = ADC_VBAT). Laisser RX0/TX0 libres pendant le flash USB.
Distribution 5V / 3V3-capteurs / GND : borniers a vis + rail header. Points de test TP1..TP4.
POWER-GATE +3V3_SW (GPIO13) — rev 0.2 : LDO DEDIE U1 (LD1117V33) alimente par le 5V commute par Q7 (IRF4905, VGS=-5V ; 0.2.1 : SOURCE sur +5V, DRAIN vers LDO_IN). R35 : rail OFF par defaut ; R48 : pull-down base Q8. JP1 FERME par defaut (rail permanent, ffp5cs) ; OTER JP1 sur les profils batterie -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
PONT DIVISEUR VBAT PERMANENT (rev 0.2, plus de coupure BS250) : R38 100k + JP12 : 1-2 = 18k (bus 12V, ffp5cs ; 14,7 V -> 2,24 V) ; 2-3 = 100k (1S Li-ion, msp/n3pp). R49/C13 filtre, D11 clamp 3V3.
PROFIL BUS 12V SOLAIRE : fusible lame 7,5-10A EN AMONT (hors carte), anti-inversion P-MOSFET Q11, TVS 18V D8 (1.5KE18A, DO-201), reservoir ; buck 12->5V EXTERNE (module MP1584/XL4015 faible Iq sur entretoises, via J36/J37 ; J37 passe par Q12).
PROFIL SECTEUR : Hi-Link HLK-20M05 EMBARQUE (5V/3,6A) + fusible T1A (porte-fusible a capot, empreinte universelle pas 22,5-22,6) + varistance 10 ou 14 mm. Le corps du module enjambe la frontiere secteur/logique (fente fraisee dessous). ZONE 230V = DANGER.
microSD : module SPI 3V3 sockete. JP2/3/4/11 : source des lignes CS/SCK/MOSI/MISO = S3 natif (1-2, defaut) ou WROOM env wroom-sd (2-3). MISO WROOM = GPIO12/MTDI : efuse VDD_SDIO=3V3 OBLIGATOIRE avant (strap tension flash).
SITE A2 : ESP32-S3-DevKitC-1 44 broches, couche, USB vers le bord droit. Rangée double 25,4 / 22,86 mm. UN SEUL module peuple (A1 OU A2). Cartographies PINMAP_UNIVERSAL des 3 firmwares.
ENTREES ANALOGIQUES PARTAGEES ADC_A..D : LDR msp (JP16-19 FERMES) ou sondes sol n3pp (JP OUVERTS). ADC_E = HumidSol msp / Luminosite n3pp / LDR ffp5cs (JP20). Pluie msp = net US1 ; DHT ext msp = net US2 (pull-up R47 si JP21 FERME) — roles disjoints.
J38 CMD SENSE : collecteurs des 6 transistors relais (0V = relais colle, 5V = repos) + GND + 5V — retour d'etat reel pour un expandeur deporte (PCF8574 via diviseur).

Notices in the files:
parts and their libraries:
Diode double empreinte : DO-35 traversant pas 7,62 mm (BAT85/BAT42/BAT43) OU SOD-123 CMS (BAT43W/BAT54) ; un seul posé. Derive de D_DO-35_SOD27_P7.62mm_Horizontal et D_SOD-123 (kicad-footprints, CC-BY-SA 4.0)
